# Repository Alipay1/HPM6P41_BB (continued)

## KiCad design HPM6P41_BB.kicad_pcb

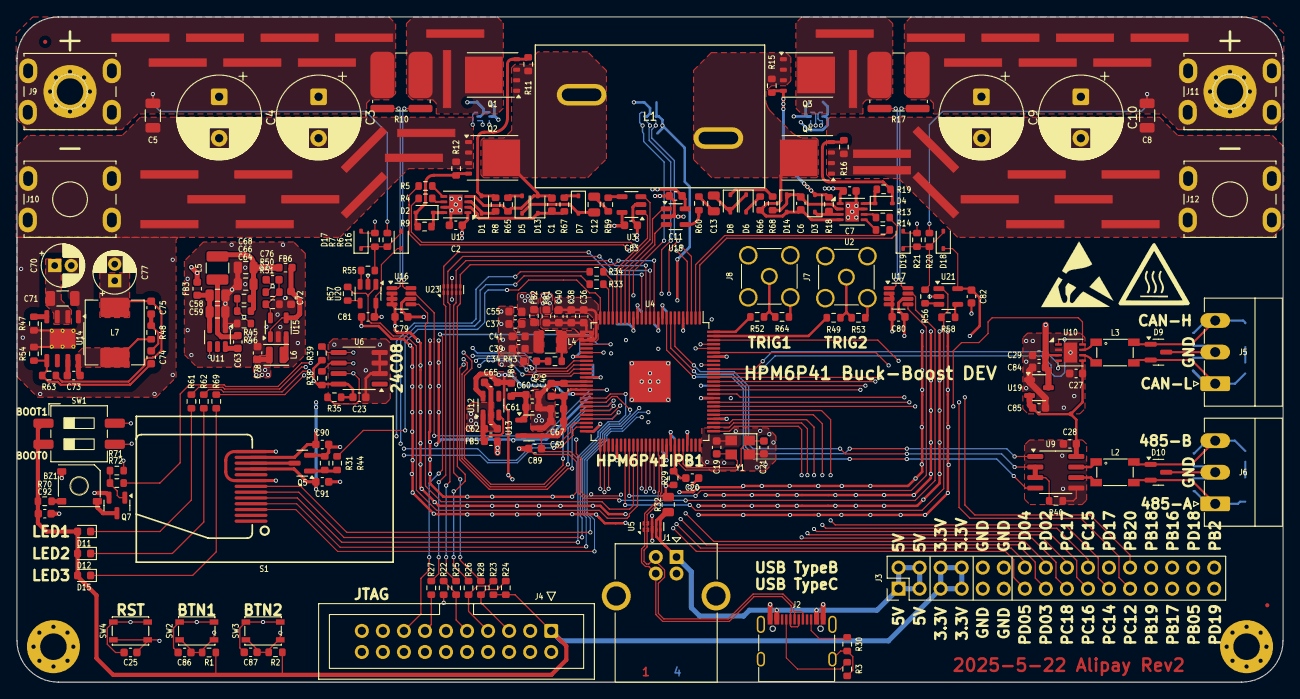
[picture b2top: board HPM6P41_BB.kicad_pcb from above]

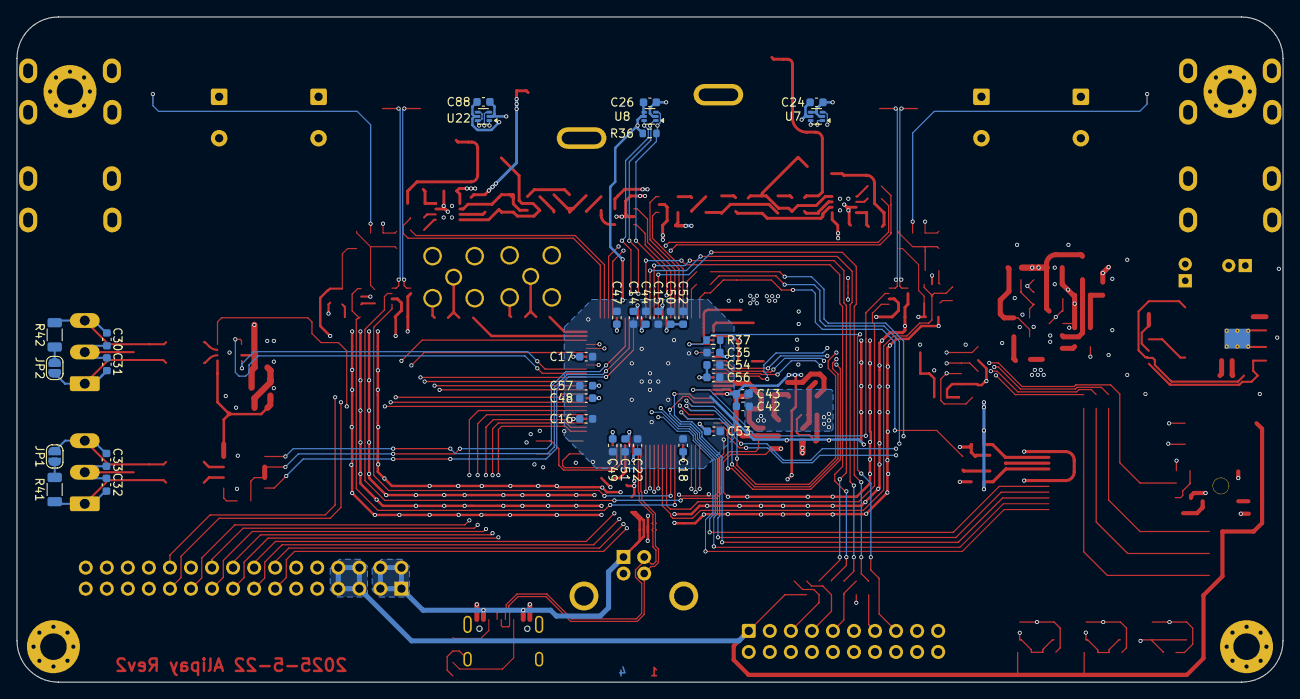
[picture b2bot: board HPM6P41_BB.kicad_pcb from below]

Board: 4 copper layers, 152.8 x 80.3 mm, 252 parts (36 on the bottom side), 165 nets.

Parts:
BZ1: Buzzer_DummyPIn3; Buzzer_5020_MetalHole
C1, C2, C6, C7: 100nF 50V; C_0603_1608Metric
C3, C4, C9, C10: 100V 100uF; CP_Radial_D10.0mm_P5.00mm
C5, C8: 10uF,50V; C_1206_3216Metric
C11, C83: 4.7uF,50V; C_0603_1608Metric
C12, C13: 1uF,100V; C_0805_2012Metric
C14, C15, C16, C17, C18, C20, C22, C35, C40, C41, C43, C44, C47, C48, C49, C51, C52, C53, C56, C61, C69, C79, C80, C81, C82, C89, C90, C91: 100nF,10V; C_0603_1608Metric
C19, C21: 6pF; C_0603_1608Metric
C23, C24, C25, C26, C27, C28, C29, C63, C86, C87, C88: 100nF; C_0603_1608Metric
C30, C31, C32, C33, C74: 47pF,50V; C_0603_1608Metric
C34: 2.2nF,10V; C_0603_1608Metric
C36, C37, C38, C39, C55, C57, C60, C72, C78: 22uF,10V; C_0603_1608Metric
C42, C46, C50, C54, C67: 4.7uF,10V; C_0603_1608Metric
C45: 10nF,10V; C_0603_1608Metric
C58: 22uF,35V; C_0805_2012Metric
C59: 100nF,50V; C_0805_2012Metric
C62, C65, C84, C85: 1uF,10V; C_0603_1608Metric
C64: 75pF; R_0603_1608Metric
C66, C68: 22uF; C_0805_2012Metric
C70: 100V 2.2uF; CP_Radial_D5.0mm_P2.00mm
C71: 1uF 100V; C_1206_3216Metric
C73: 2.2nF 50V; C_0603_1608Metric
C75: 1.2nF,50V; C_0603_1608Metric
C76: 22pF; C_0603_1608Metric
C77: 16V 47uF ±20%; CP_Radial_D5.0mm_P2.00mm
C92: 1uF; C_0603_1608Metric
D1, D2, D3, D4, D5, D6, D7, D8, D16, D17, D18, D19: 1N4148WS; D_SOD-323
D9, D10: NUP2105L; SOT-23
D11, D12, D15: LED; LED_0603_1608Metric
D13, D14: BZT52C9V1S; D_SOD-323
FB1, FB2, FB3, FB4, FB5, FB6: 100Ω@100MHz 2A; L_0603_1608Metric
FID1, FID2: Fiducial; Fiducial_0.5mm_Mask1mm
H1, H2, H3, H4: MountingHole_Pad; MountingHole_3.2mm_M3_Pad_Via
J1: USB_B; USB_B_OST_USB-B1HSxx_Horizontal
J2: USB_C_Receptacle_USB2.0_16P; USB_C_16P_On_Board
J3: Conn_02x16_Odd_Even; PinHeader_2x16_P2.54mm_Vertical
J4: Conn_ARM_JTAG_SWD_20; IDC-Header_2x10_P2.54mm_Vertical
J5, J6: Conn_01x03; PhoenixContact_MC_1,5_3-G-3.81_1x03_P3.81mm_Horizontal
J7, J8: SMA; SMA_Amphenol_901-144_Vertical
J9, J10, J11, J12: Conn_01x01; 48A_Connector_PCB_3
JP1, JP2: SolderJumper_2_Open; SolderJumper-2_P1.3mm_Open_RoundedPad1.0x1.5mm
L1: CPU2916-6R8MC/VER2923-682KL; IND_VER2923_COC
L2, L3: ACT45B-510-2P-TL003; L4532
L4, L5: 4.7uH,1.6A; L_1210_3225Metric
L6: 2.2uH; L_Changjiang_FNR252012S
L7: 68uH,1.7A,3A; L_Chilisin_BMRB00060650
Q1, Q2, Q3, Q4: HYG080N10LS1C2; TDSON-8-1
Q5, Q7: S8050; SOT-23
R1, R2, R37: 5.1k; R_0603_1608Metric
R3, R7, R21, R30, R35, R36: 5.1kΩ; R_0603_1608Metric
R4, R5, R13, R14: 33Ω; R_0603_1608Metric
R6, R20: 120kΩ; R_0603_1608Metric
R8, R9, R18, R19, R29, R43: 10Ω; R_0603_1608Metric
R10, R17: 1mΩ 5W; R_Shunt_2725_2726
R11, R12, R15, R16, R40: 10kΩ; R_0603_1608Metric
R22, R23, R24: 10K; R_0603_1608Metric
R25, R26, R27, R28, R59, R60, R65, R66: 100Ω; R_0603_1608Metric
R31, R44: 1k; R_0603_1608Metric
R32: 0R; R_0805_2012Metric
R33, R34, R55, R56, R57, R58, R67, R68: 1kΩ; R_0603_1608Metric
R38, R39: 2kΩ; R_0603_1608Metric
R41, R42: 120Ω; R_1206_3216Metric
R45: 100k; R_0603_1608Metric
R46: 13.3k; R_0603_1608Metric
R47: 76.8k; R_0603_1608Metric
R48: 309k; R_0603_1608Metric
R49, R52, R53, R64: 50Ω; R_0603_1608Metric
R50: 68k; R_0603_1608Metric
R51: 15k; R_0603_1608Metric
R54: 101k; R_0603_1608Metric
R61, R62, R69: 10k; R_0603_1608Metric
R63: 665k; R_0603_1608Metric
R70: 0R; R_0603_1608Metric
R71: 4.7k; R_0603_1608Metric
R72: 100; R_0603_1608Metric
S1: 焊接式_TFT_1.14_135X240_13PIN
SW1: 焊盘; SW_DIP_SPSTx02_Slide_6.7x6.64mm_W8.61mm_P2.54mm_LowProfile
SW2, SW3, SW4: Push_Button; LCSC_SW_SPST_PTS810
U1, U2: UCC27211ADRMR; VSON-8-1EP_3x3mm_P0.65mm_EP1.65x2.4mm
U3, U18: UCC27519; SOT-23-5
U4: HPM6P41IPB1; LQFP-100_14x14mm_P0.5mm_EP5.0x5.0mm
U5, U23: TPD4E05U06DQA; USON-10_2.5x1.0mm_P0.5mm
U6: AT24C08C-SSHM-T; SOIC-8_3.9x4.9mm_P1.27mm
U7, U8, U22: TMP112xxDRL; SOT-563
U9: SIT3088ETK; SOIC-8_3.9x4.9mm_P1.27mm
U10: TJA1044GTK/3Z; HVSON-8-1EP_3x3mm_P0.65mm_EP1.6x2.4mm
U11: TPS54302; SOT-23-6
U12: LP5907MFX-3.3; SOT-23-5
U13: REF3030; SOT-23
U14: LM5164DDA; HSOP-8-1EP_3.9x4.9mm_P1.27mm_EP2.41x3.1mm_ThermalVias
U15: SY8089; SOT-23-5
U16, U17: INA241A3xDDF; SOT-23-8
U19: XC6206PxxxMR; SOT-23-3
U20, U21: SGM8551XN; TSOT-23-5
Y1: 24MHz ±10ppm 6pF; Crystal_SMD_3225-4Pin_3.2x2.5mm

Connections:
+3.3V: C14.1, C15.1, C16.1, C17.1, C18.1, C22.1, C23.2, C24.2, C26.2, C35.1, C76.1, C78.1, C88.2, C90.1, C91.1, C92.1, D11.2 (A), D12.2 (A), D15.2 (A), FB1.1, J3.5, J3.6, J3.7, J3.8, J4.1 (VTREF), L6.1, R1.1, R2.1, R23.1, R24.1, R35.2, R36.2, R37.1, R38.2, R39.2, R50.1, R70.1, S1.10 (VCC), S1.12 (VCC), SW1.1 (PIN1), SW1.2 (PIN2), U4.10 (VIO_B00), U4.16 (VIO_B00), U4.32 (VPMC), U4.55 (VIO_B02), U4.67 (VPLLVUSB), U4.79 (VIO_B01), U4.94 (VIO_B01), U6.8 (VCC), U7.5 (V+), U8.4 (ADD0), U8.5 (V+), U22.5 (V+)
+3.3VC: C27.2, C28.2, C85.1, U9.8 (VCC), U10.5 (VIO), U19.2 (VO)
+5V: C29.2, C64.1, C66.1, C68.1, C84.1, FB5.1, FB6.1, L5.2, R29.2, R32.2, R45.1, U10.3 (VCC), U19.3 (VI)
/BB/G1: D1.2 (A), Q1.4 (G), R8.2, R11.2
/BB/G2: D2.2 (A), Q2.4 (G), R9.2, R12.2
/BB/G3: D3.2 (A), Q3.4 (G), R15.2, R18.2
/BB/G4: D4.2 (A), Q4.4 (G), R16.2, R19.2
/BB/InputIsense+: R10.2, U16.1 (-)
/BB/InputIsense-: R10.3, U16.8 (+)
/BB/InputVsense+: D16.2 (A), D17.1 (K), R6.2, R7.1, R55.1
/BB/OutputIsense+: R17.2, U17.1 (-)
/BB/OutputIsense-: R17.3, U17.8 (+)
/BB/OutputVsense+: D18.2 (A), D19.1 (K), R20.2, R21.1, R56.1
/BB/S1: C1.2, D13.2 (A), L1.1, Q1.1 (S), Q1.2 (S), Q1.3 (S), Q2.5 (D), R11.1, R65.2, U1.4 (HS)
/BB/S3: C6.2, D14.2 (A), L1.2, Q3.1 (S), Q3.2 (S), Q3.3 (S), Q4.5 (D), R15.1, R66.2, U2.4 (HS)
/J_TCK: J4.9 (TCK/SWDCLK), R22.2, R25.1
/J_TDI: J4.5 (TDI), R24.2, R28.1
/J_TDO: J4.13 (TDO/SWO), R27.1
/J_TMS: J4.7 (TMS/SWDIO), R23.2, R26.1
/MCU_MISC/RESETN: C25.2, J4.15 (~SRST), R37.2, SW4.2, U4.29 (RESET)
/MCU_MISC/XTALI: C19.1, U4.71 (XTALI), Y1.3
/MCU_MISC/XTALO: C21.1, U4.70 (XTALO), Y1.1
/MCU_PWR/LP: L4.2, R43.2, U4.27 (DCDC_LP)
/PA0: R31.2, U4.25 (PA00/GPTMR1.COMP0/UART0.TXD/PWM0.P0/TRG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)
/PA2: R33.2, U4.23 (PA02/GPTMR1.COMP1/UART0.DE/UART0.RTS/I2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)
/PA3: R34.2, U4.22 (PA03/GPTMR1.CAPT1/UART0.CTS/I2C2.SDA/SP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)
/PA4: R27.2, U4.15 (PA04/UART1.CTS/SPI1.SCLK/MCAN0.RXD/PWM0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), U23.1 (D1+), U23.10 (NC)
/PA5: R28.2, U4.14 (PA05/GPTMR1.COMP2/UART1.DE/UART1.RTS/SP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), U23.4 (D2+), U23.7 (NC)
/PA6: R25.2, U4.13 (PA06/GPTMR0.CAPT0/UART1.RXD/SPI1.MISO/P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), U23.2 (D1-), U23.9 (NC)
/PA7: R26.2, U4.12 (PA07/GPTMR0.COMP0/UART1.TXD/SPI1.MOSI/P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), U23.5 (D2-), U23.6 (NC)
/PA8: U4.9 (PA08/GPTMR0.COMP1/UART2.TXD/I2C0.SCL/SP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), U9.4 (DI)
/PA9: U4.8 (PA09/GPTMR0.CAPT1/UART2.RXD/I2C0.SDA/SP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), U9.1 (RO)
/PA10: R40.2, U4.7 (PA10/GPTMR0.COMP2/UART2.DE/UART2.RTS/SP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), U9.2 (~RE), U9.3 (DE)
/PA12: R5.2, U4.4 (PA12/UART3.CTS/I2C1.SDA/SPI0.MISO/PWM1.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)
/PA13: R4.2, U4.3 (PA13/GPTMR1.COMP3/UART3.DE/UART3.RTS/I2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)
/PA14: R14.2, U4.2 (PA14/UART3.RXD/SPI0.DAT2/MCAN1.RXD/PWM1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)
/PA15: R13.2, U4.1 (PA15/GPTMR0.COMP3/UART3.TXD/SPI0.DAT3/M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)
/PA16: U3.1 (EN), U4.21 (PA16/GPTMR3.COMP0/PWM2.P0/TRGM.P16/RDC0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)
/PA17: U3.3 (IN+), U4.20 (PA17/GPTMR3.CAPT0/PWM2.P1/TRGM.P17/RDC0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)
/PA18: U4.19 (PA18/GPTMR3.COMP1/I2C2.SCL/PWM2.P2/TRGM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), U18.1 (EN)
/PA19: U4.18 (PA19/GPTMR3.CAPT1/I2C2.SDA/MCAN0.STBY/P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), U18.3 (IN+)
/PB0: R52.2, U4.100 (PB00/GPTMR2.COMP0/XPI0.CA_SCLK/PWM0.P0/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)
/PB1: R49.2, U4.99 (PB01/GPTMR2.CAPT0/XPI0.CA_D0/PWM0.P1/TR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)
/PB2: J3.32, U4.98 (PB02/GPTMR2.COMP1/I2C2.SCL/XPI0.CA_D1/P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)
/PB3: S1.7 (CS), U4.97 (PB03/GPTMR2.CAPT1/I2C2.SDA/SPI0.CS3/MCA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)
/PB4: S1.4 (SCL), U4.96 (PB04/UART1.CTS/SPI0.SCLK/MCAN0.RXD/XPI0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)
/PB5: J3.29, U4.95 (PB05/GPTMR2.COMP2/UART1.DE/UART1.RTS/SP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)
/PB13: S1.3 (SDA), U4.92 (PB13/GPTMR2.COMP3/UART3.DE/UART3.RTS/I2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)
/PB14: U4.91 (PB14/UART3.RXD/SPI0.DAT2/MCAN1.RXD/XPI0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), U10.4 (RXD)
/PB15: U4.90 (PB15/GPTMR0.COMP3/UART3.TXD/SPI0.DAT3/M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), U10.1 (TXD)
/PB16: J3.28, U4.89 (PB16/GPTMR3.COMP0/XPI0.CB_D0/PWM2.P0/TR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)
/PB17: J3.27, U4.88 (PB17/GPTMR3.CAPT0/XPI0.CB_D1/PWM2.P1/TR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)
/PB18: J3.26, U4.87 (PB18/GPTMR3.COMP1/I2C2.SCL/XPI0.CB_D2/P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)
/PB19: J3.25, U4.86 (PB19/GPTMR3.CAPT1/I2C2.SDA/SPI2.CS3/MCA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)
/PB20: J3.24, U4.85 (PB20/UART0.CTS/MCAN0.RXD/PWM2.P4/TRGM.P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)
/PC12: J3.23, U4.83 (PC12/I2C1.SDA/SPI1.MISO/PWM1.P4/TRGM.P1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)
/PC13: U4.82 (PC13/GPTMR1.COMP3/I2C1.SCL/SPI1.MOSI/MC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), U10.8 (STB)
/PC14: J3.21, U4.81 (PC14/SPI1.DAT2/MCAN1.RXD/PWM1.P6/TRGM.P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)
/PC15: J3.20, U4.80 (PC15/GPTMR0.COMP3/SPI1.DAT3/MCAN1.TXD/P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)
/PC16: J3.19, U4.78 (PC16/GPTMR3.COMP0/PWM2.P0/TRGM.P16/ETH0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)
/PC17: J3.18, U4.77 (PC17/GPTMR3.CAPT0/PWM2.P1/TRGM.P17/ETH0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)
/PC18: J3.17, U4.76 (PC18/GPTMR3.COMP1/I2C2.SCL/PWM2.P2/TRGM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)
/PD2: J3.16, U4.64 (PD02/GPTMR1.COMP1/I2C2.SCL/SPI2.MOSI/TR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)
/PD3: J3.15, U4.63 (PD03/GPTMR1.CAPT1/I2C2.SDA/SPI2.DAT2/MC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)
/PD4: J3.14, U4.62 (PD04/UART1.CTS/SPI2.DAT3/MCAN0.RXD/TRGM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)
/PD5: J3.13, U4.61 (PD05/GPTMR1.COMP2/UART1.DE/UART1.RTS/SP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)
/PD6: R57.2, U4.60 (PD06/GPTMR0.CAPT0/UART1.RXD/SPI2.CS2/TR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), U20.1
/PD7: U4.59 (PD07/GPTMR0.COMP0/UART1.TXD/SPI2.CS1/TR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), U16.5
/PD8: U4.58 (PD08/GPTMR0.COMP1/UART2.TXD/I2C0.SCL/SP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), U17.5
/PD9: R58.2, U4.57 (PD09/GPTMR0.CAPT1/UART2.RXD/I2C0.SDA/PW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), U21.1
/PD17: J3.22, U4.53 (PD17/GPTMR3.CAPT0/PWM2.P1/TRGM.P17/ETH0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)
/PD18: J3.30, U4.52 (PD18/GPTMR3.COMP1/I2C2.SCL/PWM2.P2/TRGM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)
/PD19: J3.31, U4.51 (PD19/GPTMR3.CAPT1/I2C2.SDA/MCAN0.STBY/P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)
/PD20: C87.2, R2.2, SW3.2, U4.49 (PD20/MCAN0.RXD/PWM2.P4/TRGM.P20/ETH0.TX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)
/PD21: C86.2, R1.2, SW2.2, U4.48 (PD21/GPTMR3.COMP2/MCAN0.TXD/PWM2.P5/TRG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)
/PD22: R35.1, U4.47 (PD22/GPTMR2.CAPT0/PWM2.P6/TRGM.P22/QEI1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), U6.7 (WP)
/PD23: R36.1, U4.46 (PD23/GPTMR2.COMP0/PWM2.P7/TRGM.P23/QEI1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), U7.3 (ALERT), U8.3 (ALERT), U22.3 (ALERT)
/PD24: R38.1, U4.45 (PD24/GPTMR2.COMP1/I2C0.SCL/PWM0.P0/TRGM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), U6.6 (SCL), U7.1 (SCL), U8.1 (SCL), U22.1 (SCL)
/PD25: R39.1, U4.44 (PD25/GPTMR2.CAPT1/I2C0.SDA/PWM0.P1/TRGM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), U6.5 (SDA), U7.6 (SDA), U8.6 (SDA), U22.4 (ADD0), U22.6 (SDA)
/PD26: S1.6 (RES), U4.43 (PD26/GPTMR2.COMP2/SPI1.SCLK/PWM0.P2/TRG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)
/PD27: S1.5 (DC), U4.42 (PD27/SPI1.CS0/PWM0.P3/TRGM.P27/QEI1.A/Q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)
/PY0: R61.1, U4.33 (PY00/GPTMR3.COMP0/PWM2.P0/TRGM.P16/PGPI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)
/PY1: R62.1, U4.34 (PY01/GPTMR3.CAPT0/PWM2.P1/TRGM.P17/PGPI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)
/PY2: R69.1, U4.35 (PY02/GPTMR3.COMP1/I2C2.SCL/PWM2.P2/TRGM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)
/PY3: R72.2, U4.36 (PY03/GPTMR3.CAPT1/I2C2.SDA/MCAN0.STBY/P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)
CP_S1: C1.1, D13.1 (K), R67.1, U1.2 (HB)
CP_S3: C6.1, D14.1 (K), R68.1, U2.2 (HB)
GND: BZ1.3 (DUM), C2.2, C3.2, C4.2, C5.2, C7.2, C8.2, C9.2, C10.2, C11.2, C14.2, C15.2, C16.2, C17.2, C18.2, C19.2, C20.2, C21.2, C22.2, C23.1, C24.1, C25.1, C26.1, C27.1, C28.1, C29.1, C30.1, C31.2, C32.1, C33.2, C34.2, C35.2, C36.2, C37.2, C38.2, C39.2, C40.2, C41.2, C42.2, C43.2, C44.2, C45.2, C46.2, C47.2, C48.2, C49.2, C50.2, C51.2, C52.2, C53.2, C54.2, C55.2, C56.2, C57.2, C58.2, C59.2, C60.2, C61.2, C62.2, C65.2, C66.2, C67.2, C68.2, C69.2, C70.2, C71.2, C72.2, C77.2, C78.2, C79.2, C80.2, C81.2, C82.2, C83.2, C84.2, C85.2, C86.1, C87.1, C88.1, C89.2, C90.2, C91.2, C92.2, D9.3 (A), D10.3 (A), D17.2 (A), D19.2 (A), H1.1, H2.1, J1.4 (GND), J1.5 (Shield), J2.A1 (GND), J2.A12 (GND), J2.B1 (GND), J2.B12 (GND), J2.S1 (SHIELD), J3.9, J3.10, J3.11, J3.12, J4.4 (GND), J4.6 (GND), J4.8 (GND), J4.10 (GND), J4.12 (GND), J4.14 (GND), J4.16 (GND), J4.18 (GND), J4.20 (GND), J5.2, J6.2, J7.2 (Ext), J8.2 (Ext), J10.1, J12.1, Q2.1 (S), Q2.2 (S), Q2.3 (S), Q4.1 (S), Q4.2 (S), Q4.3 (S), Q5.2 (E), Q7.2 (E), R3.2, R7.2, R12.1, R16.1, R21.2, R22.1, R30.2, R40.1, R44.1, R46.2, R47.1, R51.2, R53.1, R54.1, R64.1, R71.1, S1.8 (GND), S1.13 (GND), SW2.1, SW3.1, SW4.1, U1.7 (VSS), U1.9 (EPAD), U2.7 (VSS), U2.9 (EPAD), U3.2 (GND), U4.28 (DCDC_GND), U4.38 (VREFL), U4.39 (VSSA), U4.101 (PAD), U5.3 (GND), U5.8 (GND), U6.2 (A1), U6.3 (A2), U6.4 (GND), U7.2 (GND), U7.4 (ADD0), U8.2 (GND), U9.5 (GND), U10.2 (GND), U10.9 (EP), U11.1 (GND), U12.2 (GND), U13.3 (GND), U14.1 (GND), U14.9 (EP), U15.2 (GND), U16.2 (GND), U16.3 (REF2), U16.4 (GND), U17.2 (GND), U17.3 (REF2), U17.4 (GND), U18.2 (GND), U19.1 (GND), U20.2 (V-), U21.2 (V-), U22.2 (GND), U23.3 (GND), U23.8 (GND), Y1.2, Y1.4
unnamed: BZ1.1 (+), R70.2
unnamed: BZ1.2 (-), Q7.3 (C)
unnamed: C12.2, R59.1
unnamed: C13.2, R60.1
unnamed: C34.1, R43.1
unnamed: C37.1, C39.1, C41.1, FB2.2, L4.1
unnamed: C74.1, C75.2, R48.2
unnamed: D1.1 (K), R8.1, U1.3 (HO)
unnamed: D2.1 (K), R9.1, U1.8 (LO)
unnamed: D3.1 (K), R18.1, U2.3 (HO)
unnamed: D4.1 (K), R19.1, U2.8 (LO)
unnamed: D5.2 (A), R65.1
unnamed: C12.1, D5.1 (K), D7.2 (A)
unnamed: D6.2 (A), R66.1
unnamed: C13.1, D6.1 (K), D8.2 (A)
unnamed: D7.1 (K), R67.2
unnamed: D8.1 (K), R68.2
unnamed: D11.1 (K), R61.2
unnamed: D12.1 (K), R62.2
unnamed: D15.1 (K), R69.2
unnamed: J2.A5 (CC1), R3.1
unnamed: J2.B5 (CC2), R30.1
unnamed: C31.1, D9.2 (K), J5.1, JP2.1 (A), L3.3
unnamed: C30.2, D9.1 (K), J5.3, L3.4, R42.1
unnamed: C32.2, D10.2 (K), J6.1, L2.3, R41.1
unnamed: C33.1, D10.1 (K), J6.3, JP1.1 (A), L2.4
unnamed: J7.1 (In), R49.1, R53.2
unnamed: J8.1 (In), R52.1, R64.2
unnamed: JP1.2 (B), R41.2
unnamed: JP2.2 (B), R42.2
unnamed: Q1.5 (D), R10.4
unnamed: Q3.5 (D), R17.1
unnamed: Q5.1 (B), R31.1, R44.2
unnamed: Q5.3 (C), S1.11 (LEDK)
unnamed: Q7.1 (B), R71.2, R72.1
unnamed: R33.1, SW1.3 (PIN3)
unnamed: R34.1, SW1.4 (PIN4)
unnamed: R5.1, U1.5 (HI)
unnamed: R4.1, U1.6 (LI)
unnamed: R14.1, U2.5 (HI)
unnamed: R13.1, U2.6 (LI)
unnamed: R59.2, U3.4 (OUT)
unnamed: C36.1, C38.1, C40.1, FB1.2, U4.26 (DCDC_IN)
unnamed: C50.1, C52.1, U4.17 (OTPCAP)
unnamed: C54.1, C56.1, U4.37 (VPMCCAP)
unnamed: C20.1, R29.1, U4.69 (VBUS)
unnamed: L2.2, U9.6 (A)
unnamed: L2.1, U9.7 (B)
unnamed: L3.1, U10.7 (CANH)
unnamed: L3.2, U10.6 (CANL)
unnamed: C63.1, U11.6 (BOOT)
unnamed: C64.2, R45.2, R46.1, U11.4 (FB)
unnamed: C63.2, L5.1, U11.2 (SW)
unnamed: C58.1, C59.1, FB3.2, U11.3 (VIN)
unnamed: C62.1, FB5.2, U12.1 (IN), U12.3 (EN)
unnamed: C60.1, C61.1, FB4.2, U13.1 (IN)
unnamed: C73.2, U14.7 (BST)
unnamed: C74.2, R54.2, R63.1, U14.5 (FB)
unnamed: R47.2, U14.4 (RON)
unnamed: C73.1, L7.1, R48.1, U14.8 (SW)
unnamed: C72.1, FB6.2, U15.1 (EN), U15.4 (IN)
unnamed: C76.2, R50.2, R51.1, U15.5 (FB)
unnamed: L6.2, U15.3 (LX)
unnamed: R60.2, U18.4 (OUT)
unnamed: R55.2, U20.3 (+)
unnamed: R57.1, U20.4 (-)
unnamed: R56.2, U21.3 (+)
unnamed: R58.1, U21.4 (-)
USB_DN: J1.3 (D+), J2.A7 (D-), J2.B7 (D-), U4.65 (PD01/GPTMR1.CAPT0/SPI2.MISO/TRGM.P01/ET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), U5.1 (D1+), U5.10 (NC)
USB_DP: J1.2 (D-), J2.A6 (D+), J2.B6 (D+), U4.66 (PD00/GPTMR1.COMP0/SPI2.SCLK/TRGM.P00/ET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), U5.2 (D1-), U5.9 (NC)
VANA: C42.1, C43.1, C65.1, C79.1, C80.1, C81.1, C82.1, D16.1 (K), D18.1 (K), FB4.1, U4.41 (VANA), U12.5 (OUT), U16.6 (V+), U17.6 (V+), U20.5 (V+), U21.5 (V+)
VBUS: J1.1 (VBUS), J2.A4 (VBUS), J2.A9 (VBUS), J2.B4 (VBUS), J2.B9 (VBUS), J3.1, J3.2, J3.3, J3.4, R32.1, U5.4 (D2+), U5.5 (D2-), U5.6 (NC), U5.7 (NC)
VDD_SOC: C44.1, C47.1, C48.1, C49.1, C51.1, C53.1, C55.1, C57.1, FB2.1, U4.5 (VDD_SOC), U4.11 (VDD_SOC), U4.31 (DCDC_SNS), U4.50 (VDD_SOC), U4.68 (VDD_SOC), U4.72 (VDD_SOC), U4.84 (VDD_SOC)
VIN: C3.1, C4.1, C5.1, C70.1, C71.1, H4.1, J9.1, R6.1, R10.1, U14.2 (VIN), U14.3 (EN/UVLO)
VOUT: C8.1, C9.1, C10.1, H3.1, J11.1, R17.4, R20.1
VREFH: C45.1, C46.1, C67.1, C69.1, C89.1, U4.40 (VREFH), U13.2 (OUT), U16.7 (REF1), U17.7 (REF1)
Vdrv: C2.1, C7.1, C11.1, C75.1, C77.1, C83.1, FB3.1, L7.2, R63.2, U1.1 (VDD), U2.1 (VDD), U3.5 (V_{DD}), U18.5 (V_{DD})

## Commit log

2025-05-19 首次提交，第一次打样的版本
2025-05-19 添加README
2025-05-22 修复VDD_SOC的SNS未连接的错误
2025-05-22 更改所有封装为SOD-323的1N4148W为1N4148WS 添加分压器的钳位二极管
2025-05-22 放置钳位二极管 修复分压器未接地
2025-05-22 交换LED与按键位置，优化布线，调整位号丝印
2025-05-22 添加JTAG接口的ESD保护
2025-05-22 添加蜂鸣器IO及走线，更改PINMUX配图
2025-05-22 修改丝印大小，位置
2025-05-23 Create main.yml
    AI生成的，我也不懂了
2025-05-23 no message
2025-05-23 删除main.yml，没用了
2025-05-23 放进Hardware目录
2025-05-23 Rename kicad-ci.yml to run_jobset.yaml
2025-05-23 尝试修复上传为空的问题
2025-05-23 添加actions文件
2025-06-14 修改了UCC27211A封装，此芯片此前的封装均错误 修改了采样线布局，为SAR ADC加入前置RC
2025-06-14 换掉UCC27519，它居然要55%VDD才到逻辑高，换成UCC2751
2025-06-18 Rev3最终版本
2025-06-18 修改PCB文件发布日期和REV信息
2025-07-03 外置核心电压SYR838以改善ADC噪声
2025-07-04 换其他电感之前暂存一下
2025-07-10 完成Rev4 电源 驱动 模拟 IO
2025-08-18 更新readme暂停通知，添加测试用例源代码
2026-01-24 rev4修改核心供电前保存（当前SYR838）
2026-01-24 修改spi_lcd例程，适应新版sdk提供的 SDK_VERSION_STRING，其他例程暂未修改
2026-01-27 小改丝印
2026-01-27 详细注释 相移例程 的 计算单元配置过程
2026-01-28 能够自由控制频率占空比相位，但是发现死区问题，下一版需要脱离硬件死区，使用比较值实现死区，避免Q1 Q4成组时脉宽不一致
2026-01-31 外置核心电压作为新的board，修改部分sdk_version_string，i2c components不能再board的cmake里选用，待解决
2026-01-31 修改can例程和文字部分，外部回环即使关闭phy仍通过，搁置
2026-01-31 修复：严重BUG！隔离器485与CAN信号完全相反！
2026-02-01 修改以适应rev4的硬件
2026-02-01 修改例程适应新版sdk与rev4硬件
2026-02-20 Rev4保存
2026-06-05 Add low-bandwidth FSBB closed loop
2026-06-05 Fix FSBB bridge arm mapping
2026-06-05 Poll ADC DMA for FSBB control
2026-06-06 Set FSBB PWM to 50 kHz
2026-06-06 Park boost leg for sync buck mode
2026-06-06 Tune sync buck loop response
2026-06-06 Keep buck control independent of VOFA
2026-06-06 Drive buck loop from divided ADC IRQ
2026-06-06 Route ADC trigger to active buck TRGO
2026-06-06 Save tested buck debug state
